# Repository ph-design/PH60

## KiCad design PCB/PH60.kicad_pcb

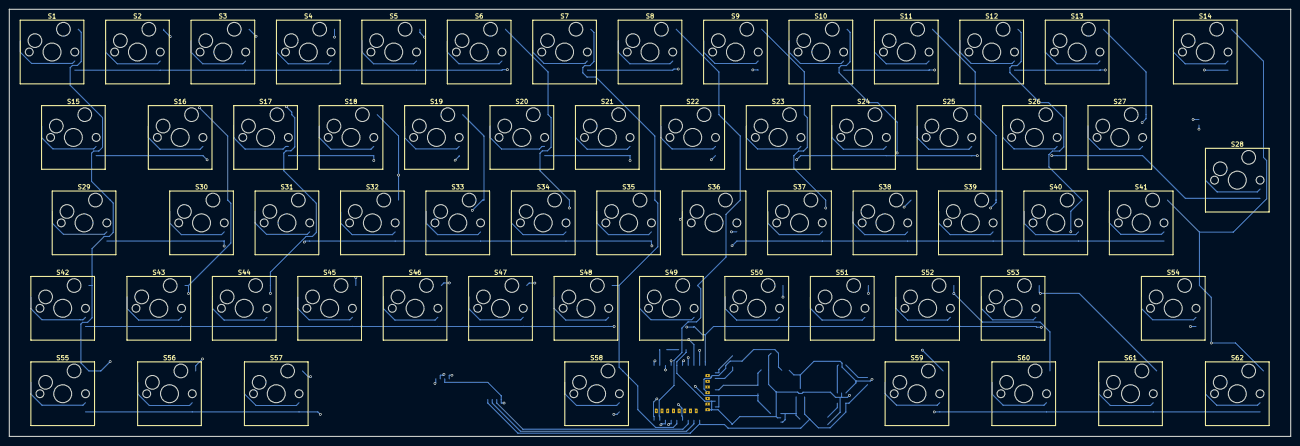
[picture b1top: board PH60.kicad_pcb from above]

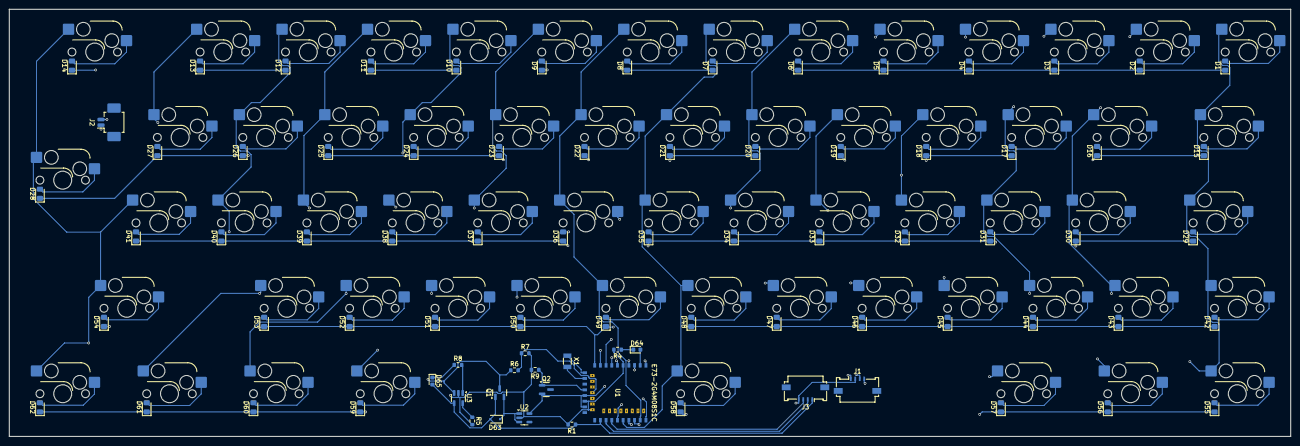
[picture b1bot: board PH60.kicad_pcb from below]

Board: 4 copper layers, 285.8 x 95.2 mm, 143 parts (81 on the bottom side), 99 nets.

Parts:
D1, D2, D3, D4, D5, D6, D7, D8, D9, D10, D11, D12, D13, D14, D15, D16, D17, D18, D19, D20, D21, D22, D23, D24, D25, D26, D27, D28, D29, D30, D31, D32, D33, D34, D35, D36, D37, D38, D39, D40, D41, D42, D43, D44, D45, D46, D47, D48, D49, D50, D51, D52, D53, D54, D55, D56, D57, D58, D59, D60, D61, D62: DIODE; D_0805_2012Metric_Pad1.15x1.40mm_HandSolder
D63: 1N5819; D_SOD-323F
D64: BLUE; LED_0603_1608Metric
D65: RED; LED_0603_1608Metric
J1, J3: Conn_01x04; Molex_200528-0040_1x04-1MP_P1.00mm_Horizontal
J2: Conn_01x02; Molex_PicoBlade_53261-0271_1x02-1MP_P1.25mm_Horizontal
Q1, Q2: AO3407; SOT-23
R1: 100K; R_0603_1608Metric
R4, R8: 1K; R_0603_1608Metric
R5: RPROG; R_0603_1608Metric
R6: 820K; R_0603_1608Metric
R7, R9: 2M; R_0603_1608Metric
S1, S2, S3, S4, S5, S6, S7, S8, S9, S10, S11, S12, S13, S16, S17, S18, S19, S20, S21, S22, S23, S24, S25, S26, S27, S30, S31, S32, S33, S34, S35, S36, S37, S38, S39, S40, S41, S43, S44, S45, S46, S47, S48, S49, S50, S51, S52, S53: MX1A; SW_Hotswap_Kailh_MX_1.00u
S14: MX1A; SW_Hotswap_Kailh_MX_2.00u
S15: MX1A; SW_Hotswap_Kailh_MX_1.50u
S28: MX1A; SW_Hotswap_Kailh_MX_ISOEnter
S29: MX1A; SW_Hotswap_Kailh_MX_1.75u
S42, S55, S56, S57, S59, S60, S61, S62: MX1A; SW_Hotswap_Kailh_MX_1.25u
S54: MX1A; SW_Hotswap_Kailh_MX_2.75u
S58: MX1A; SW_Hotswap_Kailh_MX_6.25u
U1: E73-2G4M08S1C; E73-2G4M08S1C-52840
U2: AP2112K-3.3; SOT-23-5
U3: TP4054; SOT-23-5
X1: 32768kHz; Crystal_SMD_3215-2Pin_3.2x1.5mm

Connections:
/P0.00: U1.11 (P0.00/XL1), X1.2
/P0.01: U1.13 (P0.01/XL2), X1.1
BATTERY_PIN: R6.2, R7.1, U1.18 (P0.04/AIN2)
BLUE_LED: D64.2 (A), U1.2 (P1.10)
DATA+: J3.3, U1.31 (USB_D+)
DATA-: J3.2, U1.29 (USB_D-)
GND: J1.2, J2.2, J3.4, R1.2, R4.2, R5.2, R7.2, R9.2, U1.5 (GND), U1.21 (GND), U1.24 (GND), U2.2 (GND), U3.2 (VSS)
unnamed: D1.2 (A), S1.1
unnamed: D2.2 (A), S2.1
unnamed: D3.2 (A), S3.1
unnamed: D4.2 (A), S4.1
unnamed: D5.2 (A), S5.1
unnamed: D6.2 (A), S6.1
unnamed: D7.2 (A), S7.1
unnamed: D8.2 (A), S8.1
unnamed: D9.2 (A), S9.1
unnamed: D10.2 (A), S10.1
unnamed: D11.2 (A), S11.1
unnamed: D12.2 (A), S12.1
unnamed: D13.2 (A), S13.1
unnamed: D14.2 (A), S14.1
unnamed: D15.2 (A), S15.1
unnamed: D16.2 (A), S16.1
unnamed: D17.2 (A), S17.1
unnamed: D18.2 (A), S18.1
unnamed: D19.2 (A), S19.1
unnamed: D20.2 (A), S20.1
unnamed: D21.2 (A), S21.1
unnamed: D22.2 (A), S22.1
unnamed: D23.2 (A), S23.1
unnamed: D24.2 (A), S24.1
unnamed: D25.2 (A), S25.1
unnamed: D26.2 (A), S26.1
unnamed: D27.2 (A), S27.1
unnamed: D28.2 (A), S28.1
unnamed: D29.2 (A), S29.1
unnamed: D30.2 (A), S30.1
unnamed: D31.2 (A), S31.1
unnamed: D32.2 (A), S32.1
unnamed: D33.2 (A), S33.1
unnamed: D34.2 (A), S34.1
unnamed: D35.2 (A), S35.1
unnamed: D36.2 (A), S36.1
unnamed: D37.2 (A), S37.1
unnamed: D38.2 (A), S38.1
unnamed: D39.2 (A), S39.1
unnamed: D40.2 (A), S40.1
unnamed: D41.2 (A), S41.1
unnamed: D42.2 (A), S42.1
unnamed: D43.2 (A), S43.1
unnamed: D44.2 (A), S44.1
unnamed: D45.2 (A), S45.1
unnamed: D46.2 (A), S46.1
unnamed: D47.2 (A), S47.1
unnamed: D48.2 (A), S48.1
unnamed: D49.2 (A), S49.1
unnamed: D50.2 (A), S50.1
unnamed: D51.2 (A), S51.1
unnamed: D52.2 (A), S52.1
unnamed: D53.2 (A), S53.1
unnamed: D54.2 (A), S54.1
unnamed: D55.2 (A), S55.1
unnamed: D56.2 (A), S56.1
unnamed: D57.2 (A), S57.1
unnamed: D58.2 (A), S58.1
unnamed: D59.2 (A), S59.1
unnamed: D60.2 (A), S60.1
unnamed: D61.2 (A), S61.1
unnamed: D62.2 (A), S62.1
unnamed: D63.1 (K), Q1.2 (S), U2.1 (VIN), U2.3 (EN)
unnamed: D64.1 (K), R4.1
unnamed: D65.1 (K), R8.1
unnamed: R5.1, U3.5 (PROG)
unnamed: R8.2, U3.1 (STAT)
POWER_PIN: Q2.1 (G), R9.1, U1.17 (P1.09)
SWC: J1.4, U1.39 (SWDCLK)
SWD: J1.3, U1.37 (SWDIO)
VBAT: J2.1, Q1.3 (D), R6.1, U3.3 (VBAT)
VBUS: D63.2 (A), D65.2 (A), J3.1, Q1.1 (G), R1.1, U1.27 (VBUS), U3.4 (VDD)
col_0: S1.2, S15.2, S29.2, S42.2, S55.2, U1.16 (P0.08)
col_1: S2.2, S16.2, S30.2, S43.2, S56.2, U1.14 (P0.06)
col_2: S3.2, S17.2, S31.2, S44.2, S57.2, U1.28 (P0.15)
col_3: S4.2, S18.2, S32.2, S45.2, U1.30 (P0.17)
col_4: S5.2, S19.2, S33.2, S46.2, U1.32 (P0.20)
col_5: S6.2, S20.2, S34.2, S47.2, U1.33 (P0.13)
col_6: S7.2, S21.2, S35.2, S48.2, S58.2, U1.35 (P0.24)
col_7: S8.2, S22.2, S36.2, S49.2, U1.41 (P0.09/NFC1)
col_8: S9.2, S23.2, S37.2, S50.2, U1.43 (P0.10/NFC2)
col_9: S10.2, S24.2, S38.2, S51.2, S59.2, U1.42 (P1.06)
col_10: S11.2, S25.2, S39.2, S52.2, S60.2, U1.1 (P1.11)
col_11: S12.2, S26.2, S40.2, S53.2, S61.2, U1.4 (P0.28/AIN4)
col_12: S13.2, S27.2, U1.3 (P0.03/AIN1)
col_13: S14.2, S28.2, S41.2, S54.2, S62.2, U1.6 (P1.13)
nRF_VDD: J1.1, Q2.2 (S), U1.19 (VDD), U1.23 (VDDH), U2.5 (VOUT)
row_0: D1.1 (K), D2.1 (K), D3.1 (K), D4.1 (K), D5.1 (K), D6.1 (K), D7.1 (K), D8.1 (K), D9.1 (K), D10.1 (K), D11.1 (K), D12.1 (K), D13.1 (K), D14.1 (K), U1.7 (P0.02/AIN0)
row_1: D15.1 (K), D16.1 (K), D17.1 (K), D18.1 (K), D19.1 (K), D20.1 (K), D21.1 (K), D22.1 (K), D23.1 (K), D24.1 (K), D25.1 (K), D26.1 (K), D27.1 (K), D28.1 (K), U1.8 (P0.29/AIN5)
row_2: D29.1 (K), D30.1 (K), D31.1 (K), D32.1 (K), D33.1 (K), D34.1 (K), D35.1 (K), D36.1 (K), D37.1 (K), D38.1 (K), D39.1 (K), D40.1 (K), D41.1 (K), U1.9 (P0.31/AIN7)
row_3: D42.1 (K), D43.1 (K), D44.1 (K), D45.1 (K), D46.1 (K), D47.1 (K), D48.1 (K), D49.1 (K), D50.1 (K), D51.1 (K), D52.1 (K), D53.1 (K), D54.1 (K), U1.10 (P0.30/AIN6)
row_4: D55.1 (K), D56.1 (K), D57.1 (K), D58.1 (K), D59.1 (K), D60.1 (K), D61.1 (K), D62.1 (K), U1.20 (P0.12)

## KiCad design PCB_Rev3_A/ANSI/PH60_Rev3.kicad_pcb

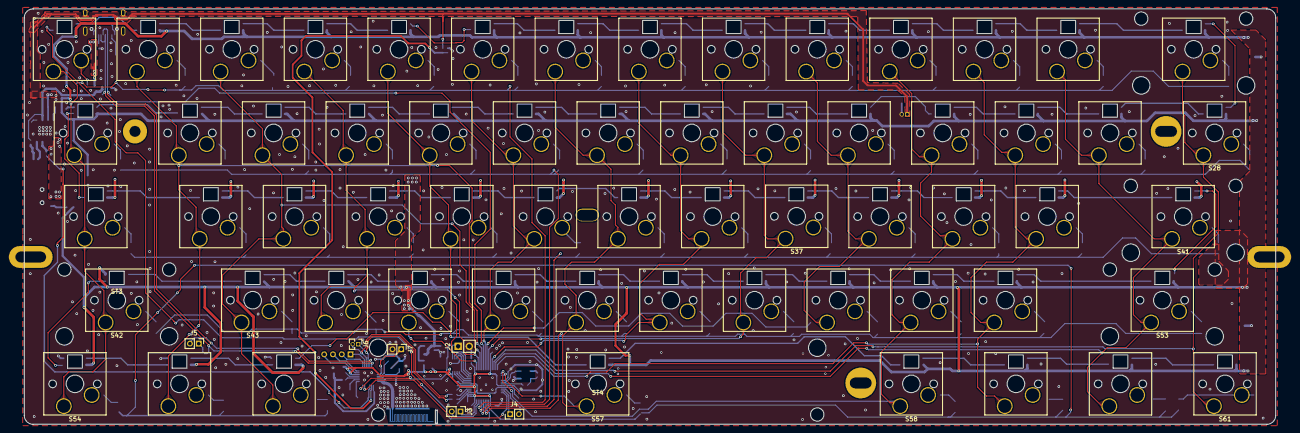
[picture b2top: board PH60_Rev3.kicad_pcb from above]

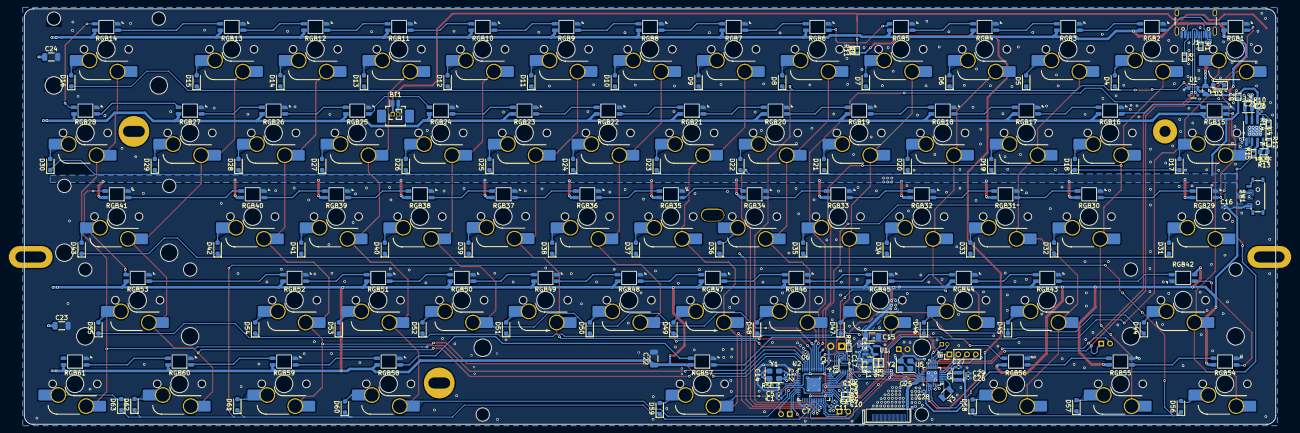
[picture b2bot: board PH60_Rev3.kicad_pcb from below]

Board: 2 copper layers, 285.0 x 94.6 mm, 264 parts (186 on the bottom side), 194 nets.

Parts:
AE1: Antenna_Shield; ANT-2.4G-1.6MM-MINI-Reversed
BT1: Battery; Molex_PicoBlade_With_Via
C1, C2, C3, C4, C5, C6, C7, C8, C9, C19: 100n; C_0402_1005Metric
C10, C11, C25: 1u; C_0402_1005Metric
C12, C14: 20p; C_0402_1005Metric
C13, C17, C20: 10u; C_0402_1005Metric
C15, C22, C23, C24: 100uF; C_1206_3216Metric
C16: 4.7u; C_0402_1005Metric
C18: 100u; C_0402_1005Metric
C21: 20u; C_0402_1005Metric
C26: 0.1u; C_0402_1005Metric
C27, C28, C29: 2u2; C_0402_1005Metric
D1: PRTR5V0U2X; SOT-143
D2: PTVS5V0P1UP; D_SOD-882_DFN1006-2
D3, D4, D5, D6, D7, D8, D9, D10, D11, D12, D13, D14, D15, D16, D17, D18, D19, D20, D21, D22, D23, D24, D25, D26, D27, D28, D29, D30, D31, D32, D33, D34, D35, D36, D37, D38, D39, D40, D41, D42, D43, D44, D45, D46, D47, D48, D49, D50, D51, D52, D53, D54, D55, D56, D57, D58, D59, D60, D61, D62, D63: DIODE; D_SOD-323_HandSoldering
F1: 1000ma; Fuse_0805_2012Metric
H1: MountingHole; PKRHC
H2, H6: MountingHole; PKRH
H3: MountingHole; PKRHHALF
H4, H5: MountingHole; PKRHSL
J1: USB_C_Receptacle_USB2.0_16P; USB-C_16P_HandSolder
J2: Conn_01x02; PinHeader_1x02_P2.54mm_Vertical
J3, J4, J5, J7: Conn_01x02_Pin; PinHeader_1x02_P2.00mm_Vertical
J6: Conn_01x02_Pin; PinHeader_1x02_P1.27mm_Vertical
J8: Conn_01x04_Pin; PinHeader_1x04_P2.00mm_Vertical
L1, L2: 2.2uH; L_Changjiang_FNR252012S
L3: 22uH; L_Changjiang_FNR252012S
R1, R2: 5K1; R_0402_1005Metric
R3, R4: 1R; R_0402_1005Metric
R5, R8: 1k; R_0402_1005Metric
R6: 442k; R_0402_1005Metric
R7, R11: 100k; R_0402_1005Metric
R9: 33k; R_0402_1005Metric
R10, R12, R13, R14, R15: 10k; R_0402_1005Metric
RGB1, RGB2, RGB3, RGB4, RGB5, RGB6, RGB7, RGB8, RGB9, RGB10, RGB11, RGB12, RGB13, RGB14, RGB15, RGB16, RGB17, RGB18, RGB19, RGB20, RGB21, RGB22, RGB23, RGB24, RGB25, RGB26, RGB27, RGB28, RGB29, RGB30, RGB31, RGB32, RGB33, RGB34, RGB35, RGB36, RGB37, RGB38, RGB39, RGB40, RGB41, RGB42, RGB43, RGB44, RGB45, RGB46, RGB47, RGB48, RGB49, RGB50, RGB51, RGB52, RGB53, RGB54, RGB55, RGB56, RGB57, RGB58, RGB59, RGB60, RGB61: WS2812B; ws2812b_6028
S1, S2, S3, S4, S5, S6, S7, S8, S9, S10, S11, S12, S13, S16, S17, S18, S19, S20, S21, S22, S23, S24, S25, S26, S27, S30, S31, S32, S33, S34, S35, S36, S37, S38, S39, S40, S43, S44, S45, S46, S47, S48, S49, S50, S51, S52: MX1A; SW_Hotswap_Kailh_MX_Plated_1.00u
S14: MX1A; SW_Hotswap_Kailh_MX_Plated_2.00u
S15, S28: MX1A; SW_Hotswap_Kailh_MX_Plated_1.50u
S29: MX1A; SW_Hotswap_Kailh_MX_Plated_1.75u
S41, S42: MX1A; SW_Hotswap_Kailh_MX_Plated_2.25u
S53: MX1A; SW_Hotswap_Kailh_MX_Plated_2.75u
S54, S55, S56, S58, S59, S60, S61: MX1A; SW_Hotswap_Kailh_MX_Plated_1.25u
S57: MX1A; SW_Hotswap_Kailh_MX_Plated_6.25u
ST0: Stabilizer_Cherry_MX_2.00u
ST1, ST2, ST3: MX_stab; Stabilizer_Cherry_MX_2.00u
ST4: MX_stab; Stabilizer_Cherry_MX_6.25u
SW1: SW_SPDT_321; SW_MSK12C02-HB
TH1: 10k_NTC; R_0603
U1: TLV62569DBV; SOT-23-5
U2: RP2040; QFN-56-1EP_7x7mm_P0.4mm_EP3.2x3.2mm
U3: W25Q16JVSS; Winbond_USON-8-1EP_3x2mm_P0.5mm_EP0.2x1.6mm
U4: LGS5500EP; SOIC-8-1EP_3.9x4.9mm_P1.27mm_EP2.41x3.3mm
U5: CH582F; QFN28_4X4_FIX
Y1: Crystal_GND24; Crystal_SMD_3225-4Pin_3.2x2.5mm
Y2: X322532MOB4SI; Crystal_SMD_3225-4Pin_3.2x2.5mm
Y3: XKXGI-SUA-32.768K; Crystal_SMD_3215-2Pin_3.2x1.5mm

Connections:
+1V1: C1.1, C2.1, C10.1, U2.23 (DVDD), U2.45 (VREG_VOUT), U2.50 (DVDD)
+3V3: C3.1, C4.1, C5.1, C6.1, C7.1, C8.1, C9.1, C11.1, C17.1, C18.1, C19.1, C27.1, L1.2, R6.1, U2.1 (IOVDD), U2.10 (IOVDD), U2.22 (IOVDD), U2.33 (IOVDD), U2.42 (IOVDD), U2.43 (ADC_AVDD), U2.44 (VREG_IN), U2.48 (USB_VDD), U2.49 (IOVDD), U3.8 (VCC), U5.5 (VIO33/VDD33)
+BATT: BT1.1 (+), C21.1, L2.2, R9.2, U4.3 (VL)
/QSPI_SCLK: U2.52 (QSPI_SCLK), U3.6 (CLK)
/QSPI_SD0: U2.53 (QSPI_SD0), U3.5 (DI/IO_{0})
/QSPI_SD1: U2.55 (QSPI_SD1), U3.2 (DO/IO_{1})
/QSPI_SD2: U2.54 (QSPI_SD2), U3.3 (~WP/IO_{2})
/QSPI_SD3: U2.51 (QSPI_SD3), U3.7 (~HOLD/~RESET/IO_{3})
/QSPI_SS: R8.2, U2.56 (QSPI_SS), U3.1 (~CS)
/RGB/rgb1: RGB42.2 (DOUT), RGB54.4 (DIN)
/RGB/rgb2: RGB42.4 (DIN), RGB43.4 (DIN)
/RGB/rgb3: RGB41.2 (DOUT), RGB53.2 (DOUT)
/RGB/rgb4: RGB56.2 (DOUT), RGB57.4 (DIN)
/RPI_RX: J3.1, U2.41 (GPIO29_ADC3)
/RPI_TX: J3.2, U2.40 (GPIO28_ADC2)
/SWCLK: J4.2, U2.24 (SWCLK)
/SWD: J4.1, U2.25 (SWD)
/XIN: C12.1, U2.20 (XIN), Y1.3
/XOUT: R5.2, U2.21 (XOUT)
/wireless/RX1: J8.4, U5.6 (PA8/RXD1/AIN12)
/wireless/SWDIO: J8.1, U5.9 (PB14/TIO/DSR_/MOSI_/PWM10)
/wireless/SWTCK: J8.2, U5.8 (PB15/TCK/MISO_/DTR_)
/wireless/TX1: J8.3, U5.7 (PA9/TMR0/TXD1/AIN13)
BOOT: J7.1, U5.17 (PB22/TMR3/RXD2_)
CHRG: R15.1, U5.24 (PA5/TXD3/AIN1)
DIN: RGB1.4 (DIN), U2.35 (GPIO23)
GND: AE1.2 (Shield), BT1.2 (-), C1.2, C2.2, C3.2, C4.2, C5.2, C6.2, C7.2, C8.2, C9.2, C10.2, C11.2, C12.2, C13.1, C14.2, C15.1, C16.2, C17.2, C18.2, C19.2, C20.2, C21.2, C22.2, C23.2, C24.2, C25.1, C26.1, C27.2, C28.2, C29.2, D1.1 (GND), J1.A1 (GND), J1.A12 (GND), J1.B1 (GND), J1.B12 (GND), J1.S1 (SHIELD), J2.2, J7.2, R1.2, R2.2, R7.2, R10.2, R11.2, R14.1, RGB1.3 (VSS), RGB2.3 (VSS), RGB3.3 (VSS), RGB4.3 (VSS), RGB5.3 (VSS), RGB6.3 (VSS), RGB7.3 (VSS), RGB8.3 (VSS), RGB9.3 (VSS), RGB10.3 (VSS), RGB11.3 (VSS), RGB12.3 (VSS), RGB13.3 (VSS), RGB14.3 (VSS), RGB15.3 (VSS), RGB16.3 (VSS), RGB17.3 (VSS), RGB18.3 (VSS), RGB19.3 (VSS), RGB20.3 (VSS), RGB21.3 (VSS), RGB22.3 (VSS), RGB23.3 (VSS), RGB24.3 (VSS), RGB25.3 (VSS), RGB26.3 (VSS), RGB27.3 (VSS), RGB28.3 (VSS), RGB29.3 (VSS), RGB30.3 (VSS), RGB31.3 (VSS), RGB32.3 (VSS), RGB33.3 (VSS), RGB34.3 (VSS), RGB35.3 (VSS), RGB36.3 (VSS), RGB37.3 (VSS), RGB38.3 (VSS), RGB39.3 (VSS), RGB40.3 (VSS), RGB41.3 (VSS), RGB42.3 (VSS), RGB43.3 (VSS), RGB44.3 (VSS), RGB45.3 (VSS), RGB46.3 (VSS), RGB47.3 (VSS), RGB48.3 (VSS), RGB49.3 (VSS), RGB50.3 (VSS), RGB51.3 (VSS), RGB52.3 (VSS), RGB53.3 (VSS), RGB54.3 (VSS), RGB55.3 (VSS), RGB56.3 (VSS), RGB57.3 (VSS), RGB58.3 (VSS), RGB59.3 (VSS), RGB60.3 (VSS), RGB61.3 (VSS), U1.2 (GND), U2.19 (TESTEN), U2.57 (GND), U3.4 (GND), U4.9 (GND), U5.0 (GND), Y1.2, Y1.4, Y2.2, Y2.4
unnamed: AE1.1 (A), U5.21 (ANT)
unnamed: C14.1, R5.1, Y1.1
unnamed: D3.2 (A), S1.1
unnamed: D4.2 (A), S2.1
unnamed: D5.2 (A), S3.1
unnamed: D6.2 (A), S4.1
unnamed: D7.2 (A), S5.1
unnamed: D8.2 (A), S6.1
unnamed: D9.2 (A), S7.1
unnamed: D10.2 (A), S8.1
unnamed: D11.2 (A), S9.1
unnamed: D12.2 (A), S10.1
unnamed: D13.2 (A), S11.1
unnamed: D14.2 (A), S12.1
unnamed: D15.2 (A), S13.1
unnamed: D16.2 (A), S14.1
unnamed: D17.2 (A), S15.1
unnamed: D18.2 (A), S16.1
unnamed: D19.2 (A), S17.1
unnamed: D20.2 (A), S18.1
unnamed: D21.2 (A), S19.1
unnamed: D22.2 (A), S20.1
unnamed: D23.2 (A), S21.1
unnamed: D24.2 (A), S22.1
unnamed: D25.2 (A), S23.1
unnamed: D26.2 (A), S24.1
unnamed: D27.2 (A), S25.1
unnamed: D28.2 (A), S26.1
unnamed: D29.2 (A), S27.1
unnamed: D30.2 (A), S28.1
unnamed: D31.2 (A), S29.1
unnamed: D32.2 (A), S30.1
unnamed: D33.2 (A), S31.1
unnamed: D34.2 (A), S32.1
unnamed: D35.2 (A), S33.1
unnamed: D36.2 (A), S34.1
unnamed: D37.2 (A), S35.1
unnamed: D38.2 (A), S36.1
unnamed: D39.2 (A), S37.1
unnamed: D40.2 (A), S38.1
unnamed: D41.2 (A), S39.1
unnamed: D42.2 (A), S40.1
unnamed: D43.2 (A), S41.1
unnamed: D44.2 (A), S42.1
unnamed: D45.2 (A), S43.1
unnamed: D46.2 (A), S44.1
unnamed: D47.2 (A), S45.1
unnamed: D48.2 (A), S46.1
unnamed: D49.2 (A), S47.1
unnamed: D50.2 (A), S48.1
unnamed: D51.2 (A), S49.1
unnamed: D52.2 (A), S50.1
unnamed: D53.2 (A), S51.1
unnamed: D54.2 (A), S52.1
unnamed: D55.2 (A), S53.1
unnamed: D56.2 (A), S54.1
unnamed: D57.2 (A), S55.1
unnamed: D58.2 (A), S56.1
unnamed: D59.2 (A), S57.1
unnamed: D60.2 (A), S58.1
unnamed: D61.2 (A), S59.1
unnamed: D62.2 (A), S60.1
unnamed: D63.2 (A), S61.1
unnamed: J1.A5 (CC1), R1.1
unnamed: J1.B5 (CC2), R2.1
unnamed: R12.2, R13.1, TH1.1
unnamed: RGB1.2 (DOUT), RGB2.4 (DIN)
unnamed: RGB2.2 (DOUT), RGB3.4 (DIN)
unnamed: RGB3.2 (DOUT), RGB4.4 (DIN)
unnamed: RGB4.2 (DOUT), RGB5.4 (DIN)
unnamed: RGB5.2 (DOUT), RGB6.4 (DIN)
unnamed: RGB6.2 (DOUT), RGB7.4 (DIN)
unnamed: RGB7.2 (DOUT), RGB8.4 (DIN)
unnamed: RGB8.2 (DOUT), RGB9.4 (DIN)
unnamed: RGB9.2 (DOUT), RGB10.4 (DIN)
unnamed: RGB10.2 (DOUT), RGB11.4 (DIN)
unnamed: RGB11.2 (DOUT), RGB12.4 (DIN)
unnamed: RGB12.2 (DOUT), RGB13.4 (DIN)
unnamed: RGB13.2 (DOUT), RGB14.4 (DIN)
unnamed: RGB14.2 (DOUT), RGB28.2 (DOUT)
unnamed: RGB15.4 (DIN), RGB29.4 (DIN)
unnamed: RGB15.2 (DOUT), RGB16.4 (DIN)
unnamed: RGB16.2 (DOUT), RGB17.4 (DIN)
unnamed: RGB17.2 (DOUT), RGB18.4 (DIN)
unnamed: RGB18.2 (DOUT), RGB19.4 (DIN)
unnamed: RGB19.2 (DOUT), RGB20.4 (DIN)
unnamed: RGB20.2 (DOUT), RGB21.4 (DIN)
unnamed: RGB21.2 (DOUT), RGB22.4 (DIN)
unnamed: RGB22.2 (DOUT), RGB23.4 (DIN)
unnamed: RGB23.2 (DOUT), RGB24.4 (DIN)
unnamed: RGB24.2 (DOUT), RGB25.4 (DIN)
unnamed: RGB25.2 (DOUT), RGB26.4 (DIN)
unnamed: RGB26.2 (DOUT), RGB27.4 (DIN)
unnamed: RGB27.2 (DOUT), RGB28.4 (DIN)
unnamed: RGB29.2 (DOUT), RGB30.4 (DIN)
unnamed: RGB30.2 (DOUT), RGB31.4 (DIN)
unnamed: RGB31.2 (DOUT), RGB32.4 (DIN)
unnamed: RGB32.2 (DOUT), RGB33.4 (DIN)
unnamed: RGB33.2 (DOUT), RGB34.4 (DIN)
unnamed: RGB34.2 (DOUT), RGB35.4 (DIN)
unnamed: RGB35.2 (DOUT), RGB36.4 (DIN)
unnamed: RGB36.2 (DOUT), RGB37.4 (DIN)
unnamed: RGB37.2 (DOUT), RGB38.4 (DIN)
unnamed: RGB38.2 (DOUT), RGB39.4 (DIN)
unnamed: RGB39.2 (DOUT), RGB40.4 (DIN)
unnamed: RGB40.2 (DOUT), RGB41.4 (DIN)
unnamed: RGB43.2 (DOUT), RGB44.4 (DIN)
unnamed: RGB44.2 (DOUT), RGB45.4 (DIN)
unnamed: RGB45.2 (DOUT), RGB46.4 (DIN)
unnamed: RGB46.2 (DOUT), RGB47.4 (DIN)
unnamed: RGB47.2 (DOUT), RGB48.4 (DIN)
unnamed: RGB48.2 (DOUT), RGB49.4 (DIN)
unnamed: RGB49.2 (DOUT), RGB50.4 (DIN)
unnamed: RGB50.2 (DOUT), RGB51.4 (DIN)
unnamed: RGB51.2 (DOUT), RGB52.4 (DIN)
unnamed: RGB52.2 (DOUT), RGB53.4 (DIN)
unnamed: RGB54.2 (DOUT), RGB55.4 (DIN)
unnamed: RGB55.2 (DOUT), RGB56.4 (DIN)
unnamed: RGB57.2 (DOUT), RGB58.4 (DIN)
unnamed: RGB58.2 (DOUT), RGB59.4 (DIN)
unnamed: RGB59.2 (DOUT), RGB60.4 (DIN)
unnamed: RGB60.2 (DOUT), RGB61.4 (DIN)
unnamed: SW1.2 (B), U4.5 (VH)
unnamed: R6.2, R7.1, U1.5 (FB)
unnamed: L1.1, U1.3 (SW)
unnamed: R4.2, U2.46 (USB_DM)
unnamed: R3.2, U2.47 (USB_DP)
unnamed: R14.2, U4.1 (ISET)
unnamed: L2.1, U4.4 (LX)
unnamed: R13.2, TH1.2, U4.8 (NTC)
unnamed: R15.2, U4.7 (VSET/LED)
unnamed: C25.2, U5.20 (VINTA)
RPI_BOOTSEL: J2.1, R8.1, U5.28 (PA12/SCS/PWM4/AIN2)
RPI_D+: J6.2, R3.1, U5.10 (PB13/U2D+/SCK0_/SCL/TXD1_)
RPI_D-: J6.1, R4.1, U5.11 (PB12/U2D-/SCS_/SDA/RXD1_)
RPI_RUN: U2.26 (RUN), U5.27 (PA13/SCK0/PWM5/AIN3)
USB_D+: D1.2 (I/O1), J1.A6 (D+), J1.B6 (D+), J5.2, U5.12 (PB11/UD+/TMR2_)
USB_D-: D1.3 (I/O2), J1.A7 (D-), J1.B7 (D-), J5.1, U5.13 (PB10/UD-/TMR1_)
VBUS: C13.2, C15.2, C16.1, C22.1, C23.1, C24.1, D2.1 (K), RGB1.1 (VDD), RGB2.1 (VDD), RGB3.1 (VDD), RGB4.1 (VDD), RGB5.1 (VDD), RGB6.1 (VDD), RGB7.1 (VDD), RGB8.1 (VDD), RGB9.1 (VDD), RGB10.1 (VDD), RGB11.1 (VDD), RGB12.1 (VDD), RGB13.1 (VDD), RGB14.1 (VDD), RGB15.1 (VDD), RGB16.1 (VDD), RGB17.1 (VDD), RGB18.1 (VDD), RGB19.1 (VDD), RGB20.1 (VDD), RGB21.1 (VDD), RGB22.1 (VDD), RGB23.1 (VDD), RGB24.1 (VDD), RGB25.1 (VDD), RGB26.1 (VDD), RGB27.1 (VDD), RGB28.1 (VDD), RGB29.1 (VDD), RGB30.1 (VDD), RGB31.1 (VDD), RGB32.1 (VDD), RGB33.1 (VDD), RGB34.1 (VDD), RGB35.1 (VDD), RGB36.1 (VDD), RGB37.1 (VDD), RGB38.1 (VDD), RGB39.1 (VDD), RGB40.1 (VDD), RGB41.1 (VDD), RGB42.1 (VDD), RGB43.1 (VDD), RGB44.1 (VDD), RGB45.1 (VDD), RGB46.1 (VDD), RGB47.1 (VDD), RGB48.1 (VDD), RGB49.1 (VDD), RGB50.1 (VDD), RGB51.1 (VDD), RGB52.1 (VDD), RGB53.1 (VDD), RGB54.1 (VDD), RGB55.1 (VDD), RGB56.1 (VDD), RGB57.1 (VDD), RGB58.1 (VDD), RGB59.1 (VDD), RGB60.1 (VDD), RGB61.1 (VDD), SW1.1 (C), U1.1 (EN), U1.4 (VIN)
VBUS_UP: F1.1, J1.A4 (VBUS), J1.A9 (VBUS), J1.B4 (VBUS), J1.B9 (VBUS)
VBUS_in: C20.1, D1.4 (VCC), D2.2 (A), F1.2, R10.1, R12.1, U4.2 (VIN)
VDCIA: C26.2, C28.1, C29.1, L3.1, U5.3 (VDCID), U5.22 (VDCIA)
VSW: L3.2, U5.4 (VSW)
X32KI: U5.2 (PA10/X32KI/TMR1), Y3.1
X32KO: U5.1 (PA11/X32KO/TMR2), Y3.2
X32MI: U5.19 (X32MI), Y2.1
X32MO: U5.18 (X32MO), Y2.3
batt_level: R9.1, R11.1, U5.23 (PA4/RXD3/AIN0)
col_0: S1.2, S15.2, S29.2, S42.2, S54.2, U2.6 (GPIO4)
col_1: S2.2, S16.2, S30.2, S55.2, U2.5 (GPIO3)
col_2: S3.2, S17.2, S31.2, S43.2, S56.2, U2.4 (GPIO2)
col_3: S4.2, S18.2, S32.2, S44.2, U2.3 (GPIO1)
col_4: S5.2, S19.2, S33.2, S45.2, U2.2 (GPIO0)
col_5: S6.2, S20.2, S34.2, S46.2, U2.7 (GPIO5)
col_6: S7.2, S21.2, S35.2, S47.2, S57.2, U2.16 (GPIO13)
col_7: S8.2, S22.2, S36.2, S48.2, U2.11 (GPIO8)
col_8: S9.2, S23.2, S37.2, S49.2, U2.9 (GPIO7)
col_9: S10.2, S24.2, S38.2, S50.2, U2.8 (GPIO6)
col_10: S11.2, S25.2, S39.2, S51.2, S58.2, U2.15 (GPIO12)
col_11: S12.2, S26.2, S40.2, S52.2, S59.2, U2.14 (GPIO11)
col_12: S13.2, S27.2, S41.2, S53.2, S60.2, U2.13 (GPIO10)
col_13: S14.2, S28.2, S61.2, U2.12 (GPIO9)
row_0: D3.1 (K), D4.1 (K), D5.1 (K), D6.1 (K), D7.1 (K), D8.1 (K), D9.1 (K), D10.1 (K), D11.1 (K), D12.1 (K), D13.1 (K), D14.1 (K), D15.1 (K), D16.1 (K), U2.39 (GPIO27_ADC1)
row_1: D17.1 (K), D18.1 (K), D19.1 (K), D20.1 (K), D21.1 (K), D22.1 (K), D23.1 (K), D24.1 (K), D25.1 (K), D26.1 (K), D27.1 (K), D28.1 (K), D29.1 (K), D30.1 (K), U2.38 (GPIO26_ADC0)
row_2: D31.1 (K), D32.1 (K), D33.1 (K), D34.1 (K), D35.1 (K), D36.1 (K), D37.1 (K), D38.1 (K), D39.1 (K), D40.1 (K), D41.1 (K), D42.1 (K), D43.1 (K), U2.37 (GPIO25)
row_3: D44.1 (K), D45.1 (K), D46.1 (K), D47.1 (K), D48.1 (K), D49.1 (K), D50.1 (K), D51.1 (K), D52.1 (K), D53.1 (K), D54.1 (K), D55.1 (K), U2.36 (GPIO24)
row_4: D56.1 (K), D57.1 (K), D58.1 (K), D59.1 (K), D60.1 (K), D61.1 (K), D62.1 (K), D63.1 (K), U2.34 (GPIO22)
